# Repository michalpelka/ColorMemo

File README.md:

# ColorMemo

An open-source, handheld color memory game built around a WeMos D1 mini (ESP8266), a 3×4 push-button matrix, a 12‑pixel NeoPixel (WS2812) LED array, and a small buzzer. 
Power it up, memorize the brief color reveal, and then flip tiles two at a time to find matching pairs. Clear the board to win and enjoy the victory animation and melody.

## Photos

Below are a few snapshots of the prototype and assembly. Images are stored in `Photos/`.

<div align="center">

</div>

<div align="center">
  
</div>

## Repository structure

- `Firmware/` — PlatformIO project with Arduino firmware for ESP8266 (D1 mini lite) using Adafruit NeoPixel.
- `KiCad/` — Complete PCB design (schematic, PCB, STEP) and production files (`gerber/`).
- `3DPrint/` — 3D printable parts for enclosure and/or fixtures.
- `Cad/` — Additional mechanical CAD sources.
- `Photos/` — Renders or placement guides.
- `LICENSE` — Project license.

## Hardware overview

- MCU: WeMos D1 mini lite (ESP8266)
- LEDs: 12× WS2812/NeoPixel (strip or array)
- Inputs: 12 momentary push buttons arranged as a 3×4 matrix (row/column scanned)
- Audio: Passive buzzer for tones and win melody

The firmware scans a 3×4 button matrix while driving a 12‑LED NeoPixel strip. On boot, it shuffles 6 color pairs, briefly reveals all 12 tiles with tones, and then hides them. Press two buttons; if the colors match, they stay lit. Match all pairs to win.

### Pinout (D1 mini lite)

- NeoPixel DIN: D1 (GPIO5)
- Buzzer: D2 (GPIO4)
- Button matrix rows (outputs):
  - ROW0: D8 (GPIO15)
  - ROW1: D3 (GPIO0)
  - ROW2: D4 (GPIO2)
- Button matrix columns (inputs with pull‑ups):
  - COL0: D0 (GPIO16)
  - COL1: D7 (GPIO13)
  - COL2: D6 (GPIO12)
  - COL3: D5 (GPIO14)
- A0 (ADC) is sampled at boot to add entropy for shuffling.

Notes:
- Columns use `INPUT_PULLUP`; a pressed button reads LOW when its row is driven active (LOW).
- The firmware maps physical grid positions to LED indices to keep the visual grid coherent.

### Bill of materials (BOM)

- KiCad BOM
- 2x3AA battery holder
- Cheap step down LM965 
- USB cable to cut 

## Firmware

The firmware lives in `Firmware/` and is a PlatformIO project.

- Board environment: `d1_mini_lite`
- Platform: `espressif8266`
- Framework: `arduino`
- Dependency: `Adafruit NeoPixel`

### Quick start (PlatformIO CLI)

1. Install PlatformIO Core (CLI): https://platformio.org/install/cli
2. From the repository root (or `Firmware/`):
   - Build: `pio run -e d1_mini_lite`
   - Upload (adjust serial port if needed): `pio run -e d1_mini_lite -t upload`
   - Serial monitor (optional): `pio device monitor`

Alternatively, use the PlatformIO IDE extension in VS Code and pick the `d1_mini_lite` environment.

## PCB and fabrication

- Open `KiCad/ColorMemo/ColorMemo.kicad_pro` in KiCad 7+
- You need to handsolder 

## 3D printing

3MF are available in `./cad`. Source is available in OnShape https://cad.onshape.com/documents/b4ecd71daf39ea8c1ed2c249/w/92a4c2cfa870c08fc1134c94/e/b7d8f3f5da42c53fd1b61ef6.

## How to play

1. Power on: all 12 tiles briefly reveal colors with tones.
2. Press a button to reveal a tile; press a second button to reveal another.
3. If they match, both remain lit. If not, they hide after a short delay.
4. Match all pairs (6 pairs total) to trigger the win animation + melody.

## Project status

- Working prototype firmware and hardware files are present.

## License

This project is licensed under the terms in `LICENSE`.

## Acknowledgements

- Adafruit NeoPixel library (MIT): https://github.com/adafruit/Adafruit_NeoPixel
- PlatformIO ecosystem for painless embedded builds

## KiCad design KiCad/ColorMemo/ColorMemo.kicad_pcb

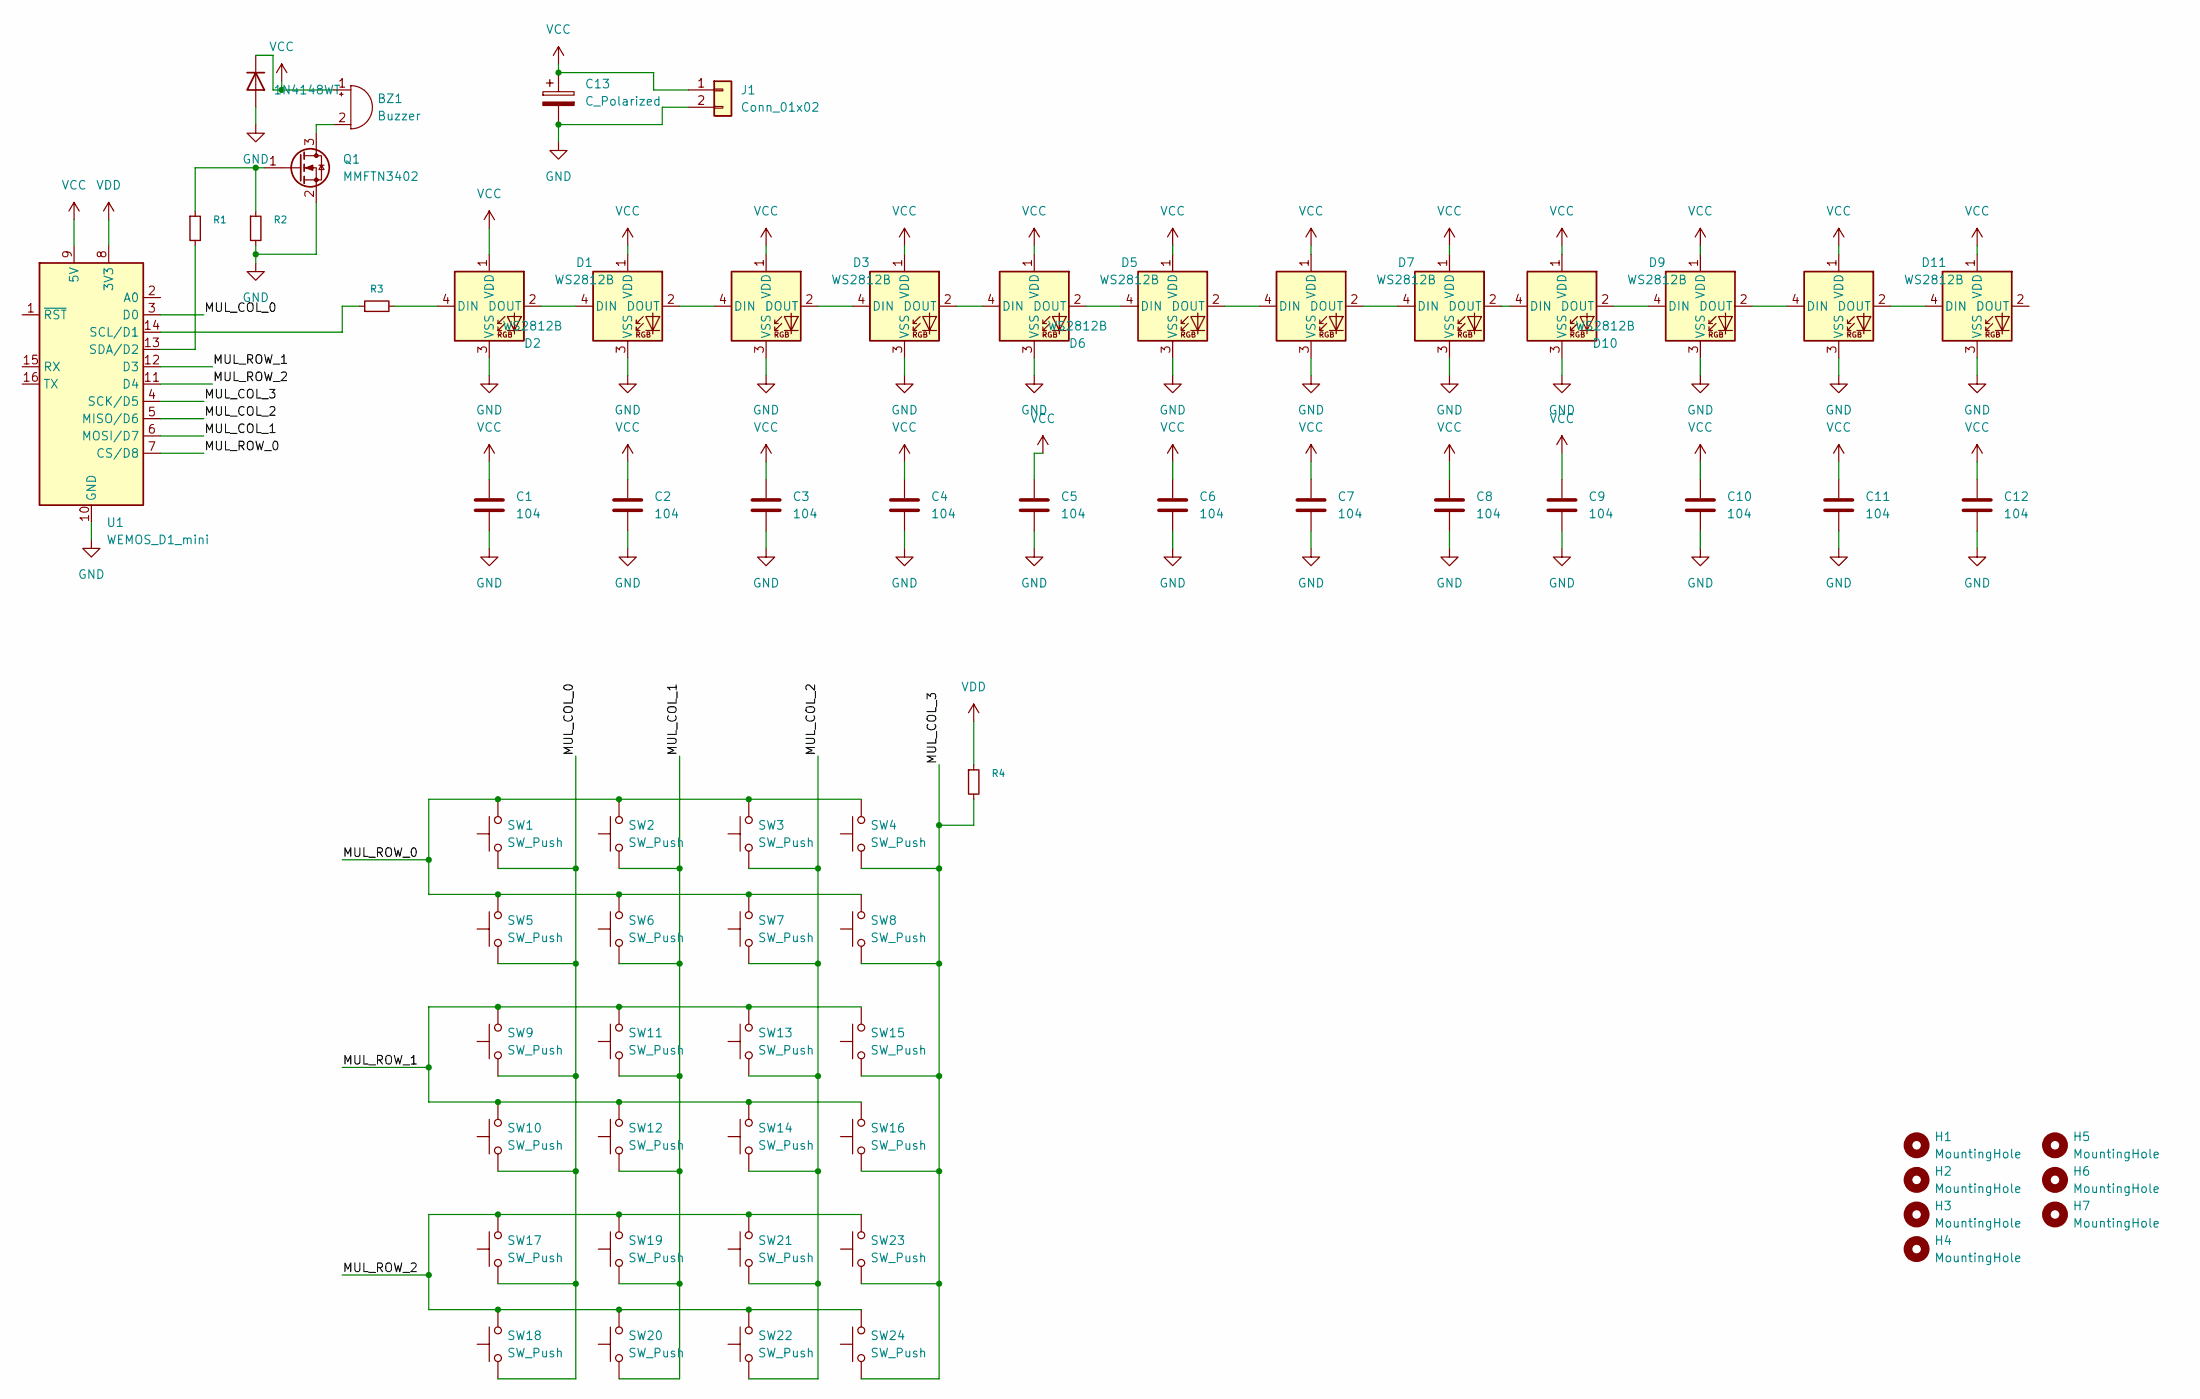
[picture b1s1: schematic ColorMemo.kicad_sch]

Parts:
BZ1: Buzzer; Buzzer_12x9.5RM7.6
C1, C2, C3, C4, C5, C6, C7, C8, C9, C10, C11, C12: 104; C_0603_1608Metric
C13: C_Polarized; CP_Radial_D8.0mm_P5.00mm
D1, D2, D3, D4, D5, D6, D7, D8, D9, D10, D11, D12: WS2812B; LED_WS2812B_PLCC4_5.0x5.0mm_P3.2mm
D13: 1N4148WT; D_SOD-523
H1, H2, H3, H4, H5, H6, H7: MountingHole; MountingHole_3.2mm_M3
J1: Conn_01x02; JST_PH_B2B-PH-K_1x02_P2.00mm_Vertical
Q1: MMFTN3402; SOT-23
R1: R100; R_0805_2012Metric_Pad1.20x1.40mm_HandSolder
R2: 100k; R_0805_2012Metric_Pad1.20x1.40mm_HandSolder
R3: R330; R_0805_2012Metric_Pad1.20x1.40mm_HandSolder
R4: 10k; R_0805_2012Metric_Pad1.20x1.40mm_HandSolder
SW1, SW2, SW3, SW4, SW5, SW6, SW7, SW8, SW9, SW10, SW11, SW12, SW13, SW14, SW15, SW16, SW17, SW18, SW19, SW20, SW21, SW22, SW23, SW24: SW_Push; SW_PUSH_6mm
U1: WEMOS_D1_mini; WEMOS_D1_mini_light

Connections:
/MUL_COL_0: SW1.1, SW5.1, SW9.1, SW10.1, SW17.1, SW18.1, U1.3 (D0)
/MUL_COL_1: SW2.1, SW6.1, SW11.1, SW12.1, SW19.1, SW20.1, U1.6 (MOSI/D7)
/MUL_COL_2: SW3.1, SW7.1, SW13.1, SW14.1, SW21.1, SW22.1, U1.5 (MISO/D6)
/MUL_COL_3: R4.2, SW4.1, SW8.1, SW15.1, SW16.1, SW23.1, SW24.1, U1.4 (SCK/D5)
/MUL_ROW_0: SW1.2, SW2.2, SW3.2, SW4.2, SW5.2, SW6.2, SW7.2, SW8.2, U1.7 (CS/D8)
/MUL_ROW_1: SW9.2, SW10.2, SW11.2, SW12.2, SW13.2, SW14.2, SW15.2, SW16.2, U1.12 (D3)
/MUL_ROW_2: SW17.2, SW18.2, SW19.2, SW20.2, SW21.2, SW22.2, SW23.2, SW24.2, U1.11 (D4)
GND: C1.2, C2.2, C3.2, C4.2, C5.2, C6.2, C7.2, C8.2, C9.2, C10.2, C11.2, C12.2, C13.2, D1.3 (VSS), D2.3 (VSS), D3.3 (VSS), D4.3 (VSS), D5.3 (VSS), D6.3 (VSS), D7.3 (VSS), D8.3 (VSS), D9.3 (VSS), D10.3 (VSS), D11.3 (VSS), D12.3 (VSS), D13.2 (A), J1.2, Q1.2 (S), R2.2, U1.10 (GND)
unnamed: BZ1.2 (-), Q1.3 (D)
unnamed: D1.4 (DIN), R3.2
unnamed: D1.2 (DOUT), D2.4 (DIN)
unnamed: D2.2 (DOUT), D3.4 (DIN)
unnamed: D3.2 (DOUT), D4.4 (DIN)
unnamed: D4.2 (DOUT), D5.4 (DIN)
unnamed: D5.2 (DOUT), D6.4 (DIN)
unnamed: D6.2 (DOUT), D7.4 (DIN)
unnamed: D7.2 (DOUT), D8.4 (DIN)
unnamed: D8.2 (DOUT), D9.4 (DIN)
unnamed: D9.2 (DOUT), D10.4 (DIN)
unnamed: D10.2 (DOUT), D11.4 (DIN)
unnamed: D11.2 (DOUT), D12.4 (DIN)
unnamed: Q1.1 (G), R1.1, R2.1
unnamed: R3.1, U1.14 (SCL/D1)
unnamed: R1.2, U1.13 (SDA/D2)
VCC: BZ1.1 (+), C1.1, C2.1, C3.1, C4.1, C5.1, C6.1, C7.1, C8.1, C9.1, C10.1, C11.1, C12.1, C13.1, D1.1 (VDD), D2.1 (VDD), D3.1 (VDD), D4.1 (VDD), D5.1 (VDD), D6.1 (VDD), D7.1 (VDD), D8.1 (VDD), D9.1 (VDD), D10.1 (VDD), D11.1 (VDD), D12.1 (VDD), D13.1 (K), J1.1, U1.9 (5V)
VDD: R4.1, U1.8 (3V3)

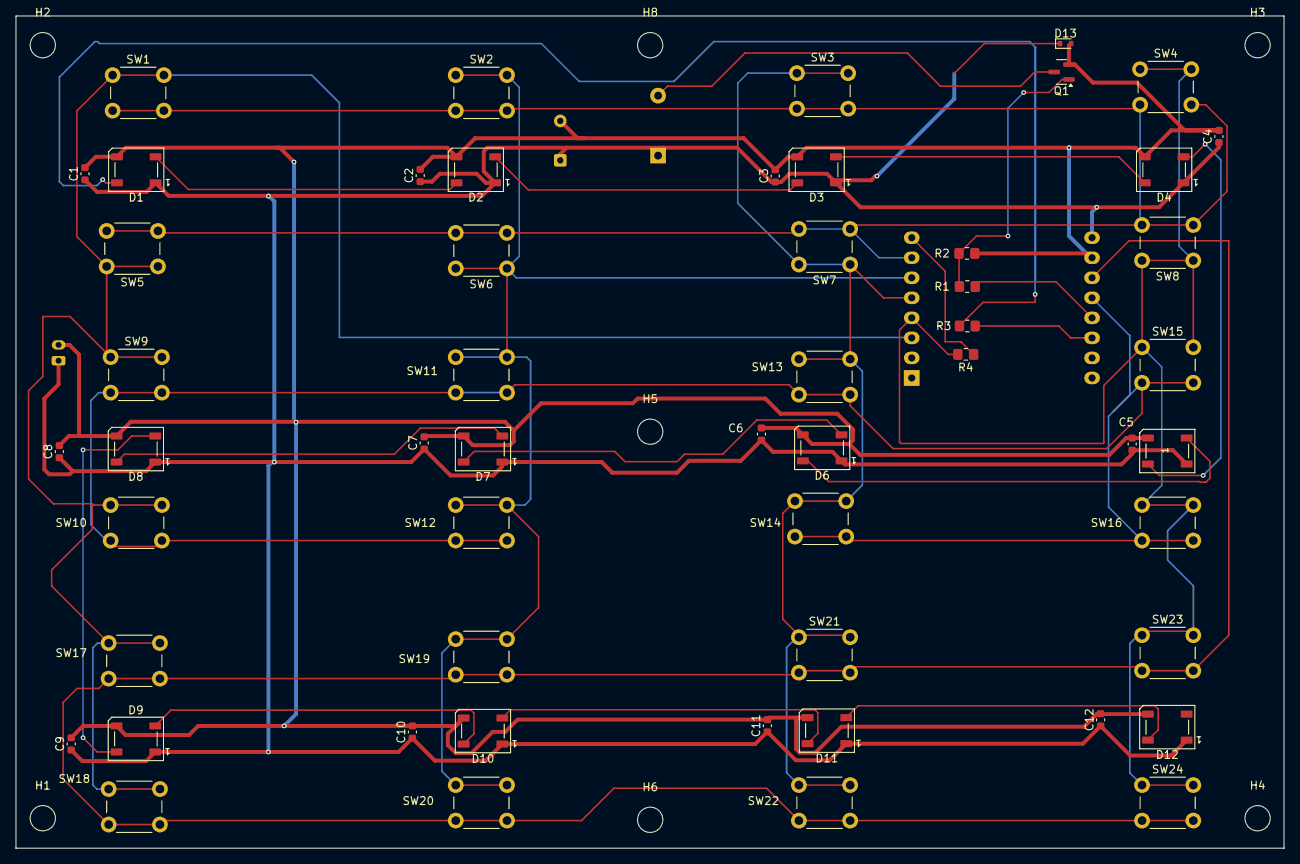
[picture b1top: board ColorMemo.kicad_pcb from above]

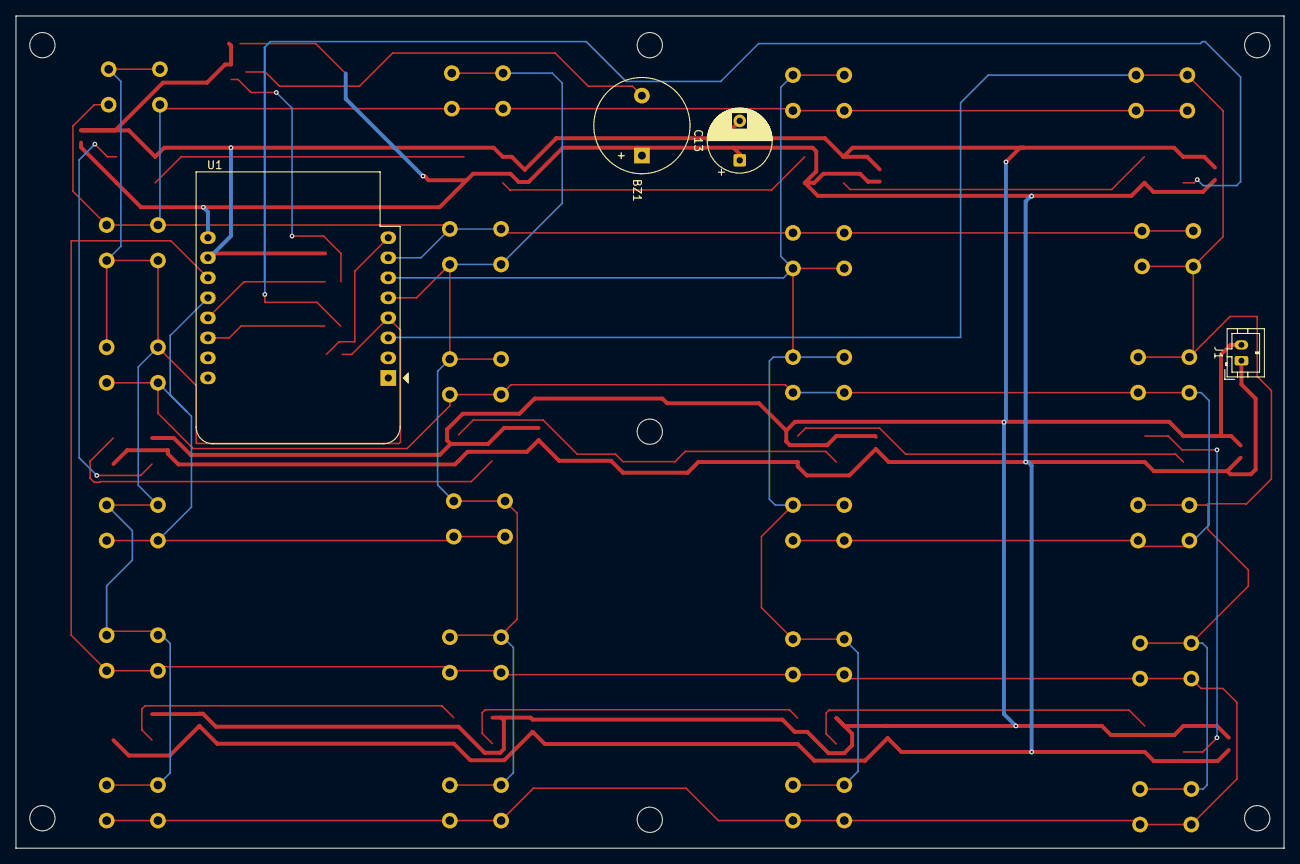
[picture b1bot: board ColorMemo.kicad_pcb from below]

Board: 2 copper layers, 160.8 x 105.5 mm, 66 parts (4 on the bottom side), 26 nets.

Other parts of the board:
H8: MountingHole; MountingHole_3.2mm_M3

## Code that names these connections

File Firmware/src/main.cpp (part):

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#define BUZZER_PIN D2 
#define NUM_LEDS  12        // change to your strip length

#define MUL_ROW_0 D8
#define MUL_ROW_1 D3
#define MUL_ROW_2 D4

#define MUL_COL_0 D0
#define MUL_COL_1 D7
#define MUL_COL_2 D6
#define MUL_COL_3 D5



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  {8, 9, 10, 11}
};

const uint8_t RowPins[ROWS] = {MUL_ROW_0, MUL_ROW_1, MUL_ROW_2};
const uint8_t colPins[COLS] = {MUL_COL_0, MUL_COL_1, MUL_COL_2, MUL_COL_3};

// Use NEO_GRBW for RGBW chips (4 channels per pixel) + NEO_KHZ800 for timing
Adafruit_NeoPixel strip(NUM_LEDS, LED_PIN, NEO_GRB + NEO_KHZ800);
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
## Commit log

2025-09-25 Initial Code added
2025-09-25 kicad
2025-09-28 added kicad project
2025-09-29 order to jlcpcb
2025-11-04 Added readme, CAD
